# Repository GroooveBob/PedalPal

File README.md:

# PedalPal
inclusive keyboard and/or footpedal board

special thanks to pcbway for supporting the development

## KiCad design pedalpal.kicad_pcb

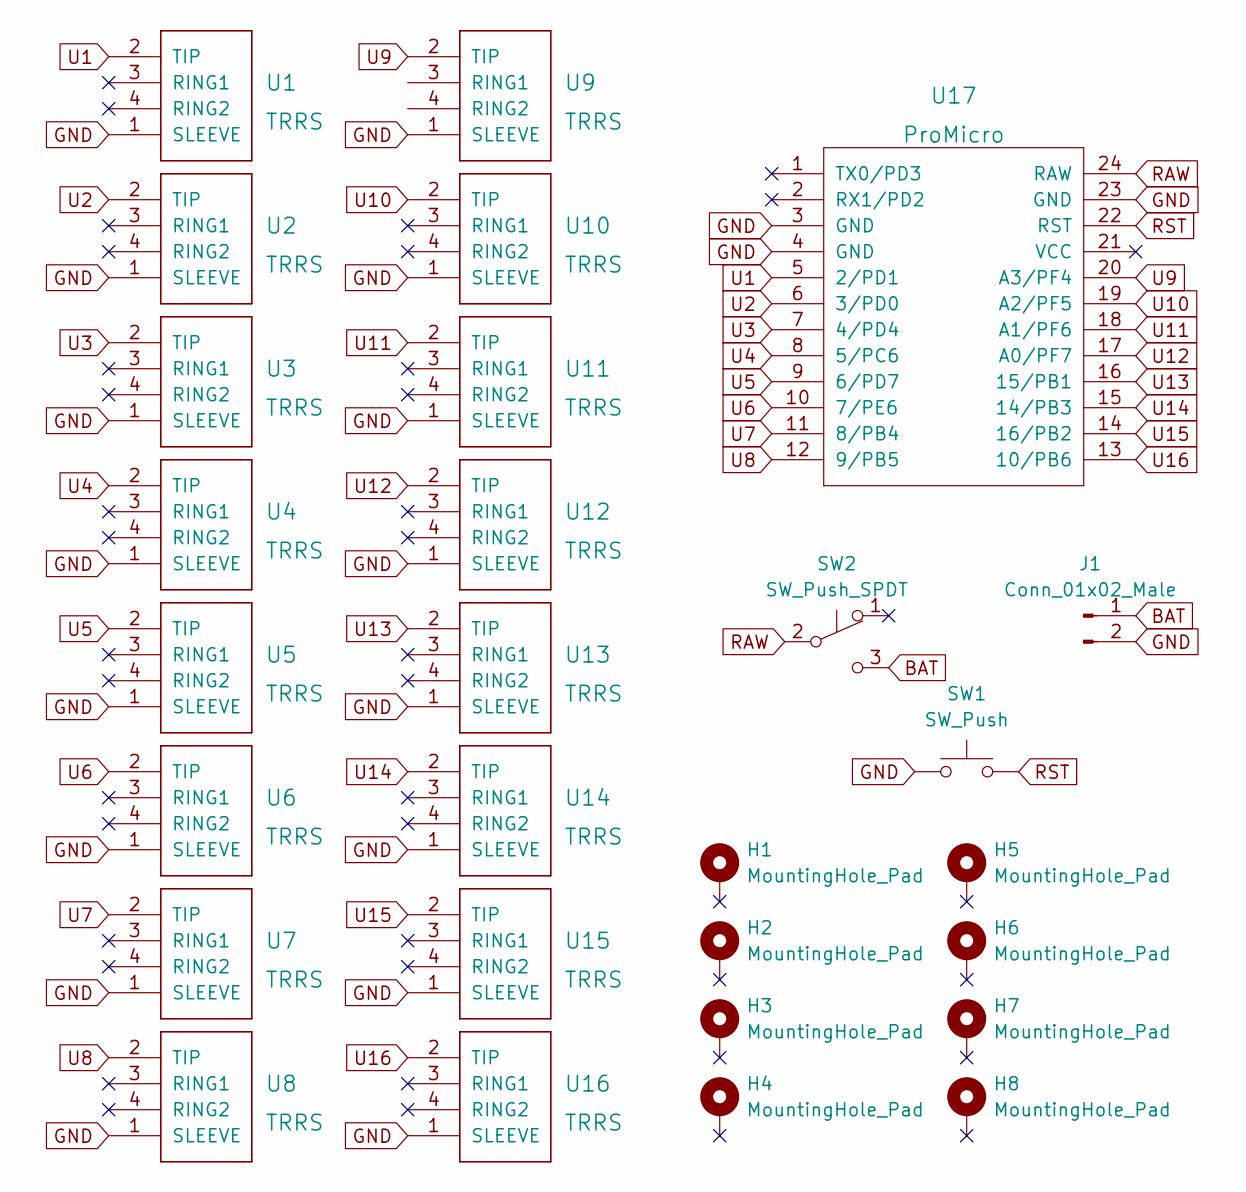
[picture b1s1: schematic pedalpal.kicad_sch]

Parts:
H1, H2, H3, H4, H5, H6, H7, H8: MountingHole_Pad; MountingHole_2.2mm_M2_DIN965_Pad
J1: Conn_01x02_Male; JST_EH_B2B-EH-A_1x02_P2.50mm_Vertical
SW1: SW_Push; ResetSW
SW2: SW_Push_SPDT; SW_SPDT_PCM12
U1, U2, U3, U4, U5, U6, U7, U8, U9, U10, U11, U12, U13, U14, U15, U16: TRRS; TRRS-PJ-320A
U17: ProMicro; ProMicro-NoSilk

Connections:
BAT: J1.1, SW2.3 (C)
GND: J1.2, SW1.1, U1.1 (SLEEVE), U2.1 (SLEEVE), U3.1 (SLEEVE), U4.1 (SLEEVE), U5.1 (SLEEVE), U6.1 (SLEEVE), U7.1 (SLEEVE), U8.1 (SLEEVE), U9.1 (SLEEVE), U10.1 (SLEEVE), U11.1 (SLEEVE), U12.1 (SLEEVE), U13.1 (SLEEVE), U14.1 (SLEEVE), U15.1 (SLEEVE), U16.1 (SLEEVE), U17.3 (GND), U17.4 (GND), U17.23 (GND)
RAW: SW2.2 (B), U17.24 (RAW)
RST: SW1.2, U17.22 (RST)
U1: U1.2 (TIP), U17.5 (2/PD1)
U2: U2.2 (TIP), U17.6 (3/PD0)
U3: U3.2 (TIP), U17.7 (4/PD4)
U4: U4.2 (TIP), U17.8 (5/PC6)
U5: U5.2 (TIP), U17.9 (6/PD7)
U6: U6.2 (TIP), U17.10 (7/PE6)
U7: U7.2 (TIP), U17.11 (8/PB4)
U8: U8.2 (TIP), U17.12 (9/PB5)
U9: U9.2 (TIP), U17.20 (A3/PF4)
U10: U10.2 (TIP), U17.19 (A2/PF5)
U11: U11.2 (TIP), U17.18 (A1/PF6)
U12: U12.2 (TIP), U17.17 (A0/PF7)
U13: U13.2 (TIP), U17.16 (15/PB1)
U14: U14.2 (TIP), U17.15 (14/PB3)
U15: U15.2 (TIP), U17.14 (16/PB2)
U16: U16.2 (TIP), U17.13 (10/PB6)

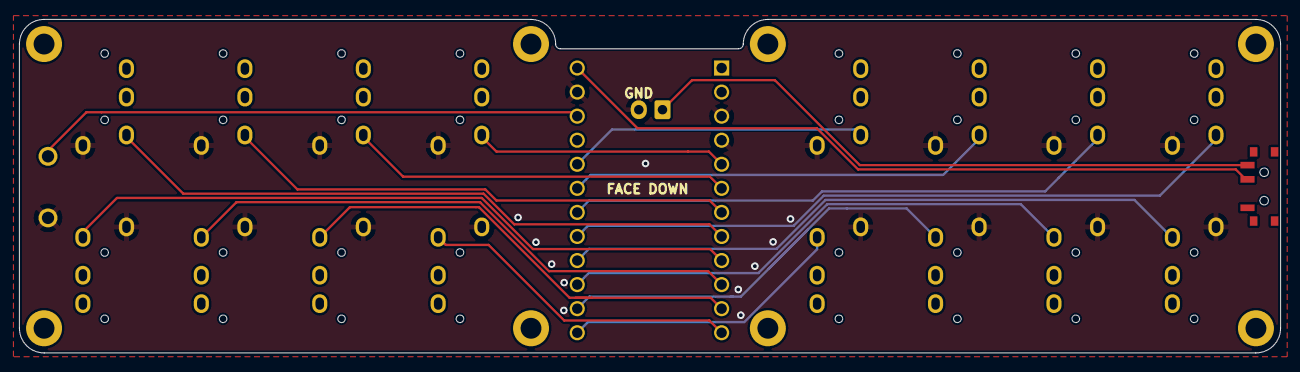
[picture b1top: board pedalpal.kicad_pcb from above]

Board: 2 copper layers, 133.1 x 35.2 mm, 28 parts (1 on the bottom side), 20 nets.

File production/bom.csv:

Designator,Footprint,Quantity,Value,LCSC Part #
U12,TRRS-PJ-320A,1,TRRS,
H3,MountingHole_2.2mm_M2_DIN965_Pad,1,MountingHole_Pad,
U16,TRRS-PJ-320A,1,TRRS,
U2,TRRS-PJ-320A,1,TRRS,
H6,MountingHole_2.2mm_M2_DIN965_Pad,1,MountingHole_Pad,
H1,MountingHole_2.2mm_M2_DIN965_Pad,1,MountingHole_Pad,
SW2,SW_SPDT_PCM12,1,SW_Push_SPDT,
U13,TRRS-PJ-320A,1,TRRS,
U10,TRRS-PJ-320A,1,TRRS,
J1,JST_EH_B2B-EH-A_1x02_P2.50mm_Vertical,1,Conn_01x02_Male,
U5,TRRS-PJ-320A,1,TRRS,
U7,TRRS-PJ-320A,1,TRRS,
H4,MountingHole_2.2mm_M2_DIN965_Pad,1,MountingHole_Pad,
H5,MountingHole_2.2mm_M2_DIN965_Pad,1,MountingHole_Pad,
H2,MountingHole_2.2mm_M2_DIN965_Pad,1,MountingHole_Pad,
U9,TRRS-PJ-320A,1,TRRS,
H7,MountingHole_2.2mm_M2_DIN965_Pad,1,MountingHole_Pad,
SW1,ResetSW,1,SW_Push,
U11,TRRS-PJ-320A,1,TRRS,
U4,TRRS-PJ-320A,1,TRRS,
U1,TRRS-PJ-320A,1,TRRS,
U6,TRRS-PJ-320A,1,TRRS,
H8,MountingHole_2.2mm_M2_DIN965_Pad,1,MountingHole_Pad,
U3,TRRS-PJ-320A,1,TRRS,
U14,TRRS-PJ-320A,1,TRRS,
U8,TRRS-PJ-320A,1,TRRS,
U15,TRRS-PJ-320A,1,TRRS,
U17,ProMicro-NoSilk,1,ProMicro,

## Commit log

2023-06-07 vial
